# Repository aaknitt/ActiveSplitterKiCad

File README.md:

# ActiveSplitter Multicoupler
Hardware design for an active RF splitter for use with RTL-SDR receivers in the 100 MHz to 1 GHz band.  Not intended to be a piece of precision test equipment, but something inexpensive and "good enough" to use for general radio monitoring and scanning activities in a smaller and more convenient form factor than cable TV splitters or conventional higher end multicouplers.  

Uses amplifier circuit from [this LNA](https://github.com/fabiobaltieri/lna) design.

Design files are in KiCad format.

Estimated cost to build is $40 to $50 in low quantities with U.S. sourced parts.  Could be as low as $10 BOM cost with overseas sourcing and higher quantities.  

## NOTE: I've built one and it seems to function about as intended, but I haven't measured performance using real test equipment yet.  

- Designed to connect four RTL-SDR USB receivers to a single antenna without insertion loss.
- Amplifier circuit provides about 18 dB to 20 dB of gain.  Four way resistive divider results in 12 dB of loss per output, so total is about 6 dB of gain to each port.
- Amplifier is designed to be powered from an SDR providing 3 to 5 volts DC power to the J1 RF output port via a bias tee or from regulated external power.
- Spacing of the output SMA connectors is designed to accomodate plugging the SDR sticks directly into [this](https://www.amazon.com/gp/aw/d/B083XTKV8V) four-port powered USB hub.
- Main board and cover are PCBs.  "Sides" of the box are formed by .1" header pins soldered to each board.  The images show all pins populated, but only every fourth or so is probably need to provide sufficient RF shielding.
- Images below show using one SMA jack for the input and four SMA plugs for outputs connected directly to the RTL-SDR dongles.  However, these can all be substituted for varying SMA genders and orientations (90 degree vs. straight) to accomodate different configurations and cables.
- PCB footprints are included for 50 ohm terminating resistors for any unused outputs.  

## Questions for reviewers:
- Nearly all RF splitter/combiner circuits that I reviewed seemed to be carefuly about maintaining symmetry in the length of all PCB traces in each "branch" of the split.  How important is this, and why?  Is there an "acceptable" amount of assymetery relative to wavelength?  Giving up symmetry would likely allow the PCB to shrink in overall size a bit.  For example, could use a single 4-port splitter instead of two 2-port splits.  That should also increase port to port isolation across adjacent ports.  
- I had originally planned to include a Pi attenuator between the output of the amplifier and the first split to further knock down excessive gain from the amplifier so that insertion loss would cancel out gain.  As it stands, there will probably be about 6 to 8 dB of gain from input to each output.  Is there any reason that could cause problems?  Should I try to add the attenuator back in, even if it makes the overall size larger?
- Will the .1" pin headers create a reasonable Faraday cage instead of a solid housing?
- Is there any advantage or reason to combine R6 with R8  and R5 with R7?
- Should the splitter that starts with R6 be closer to R8 (same with R5/R7)?
- Is the circuit providing DC power to the amplifier (L1, L2, C2) reasonable?
- Should the values of C1 and C3 be changed to support the target range of 100 MHz to 1 GHz?

Assembled View:

Schematic [PDF](https://github.com/aaknitt/ActiveSplitterKiCad/blob/main/ActiveSplitterSchematic.pdf):

Main PCB View 1:

Main PCB View 2:

Cover PCB:

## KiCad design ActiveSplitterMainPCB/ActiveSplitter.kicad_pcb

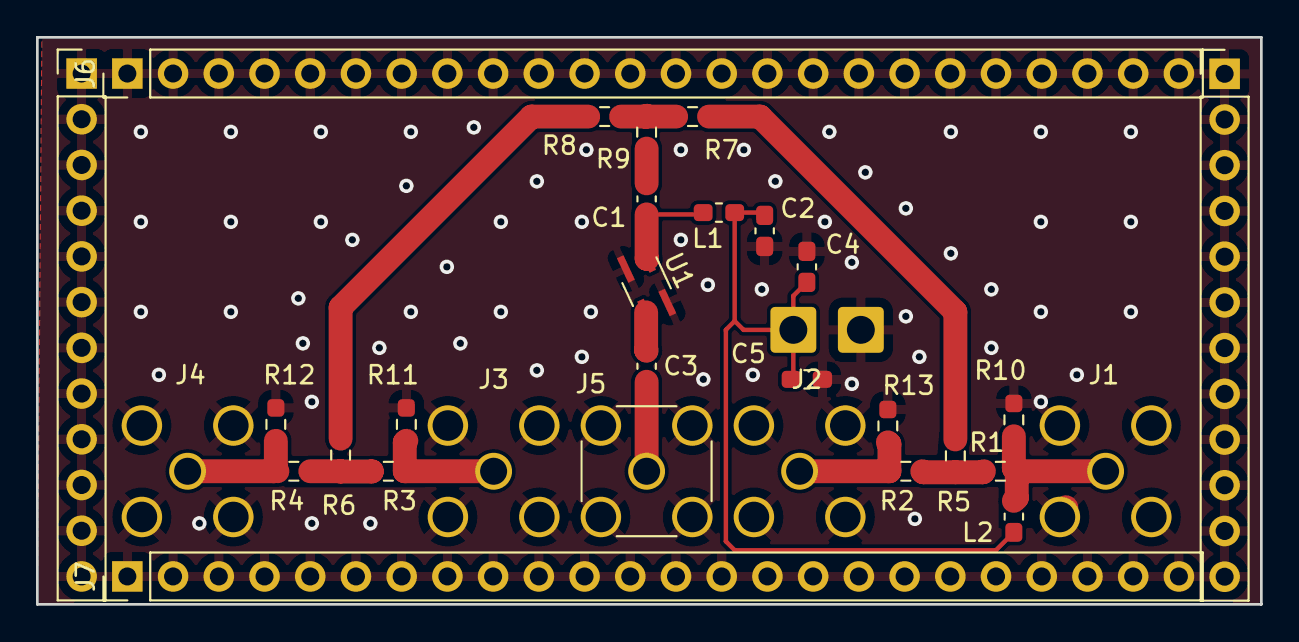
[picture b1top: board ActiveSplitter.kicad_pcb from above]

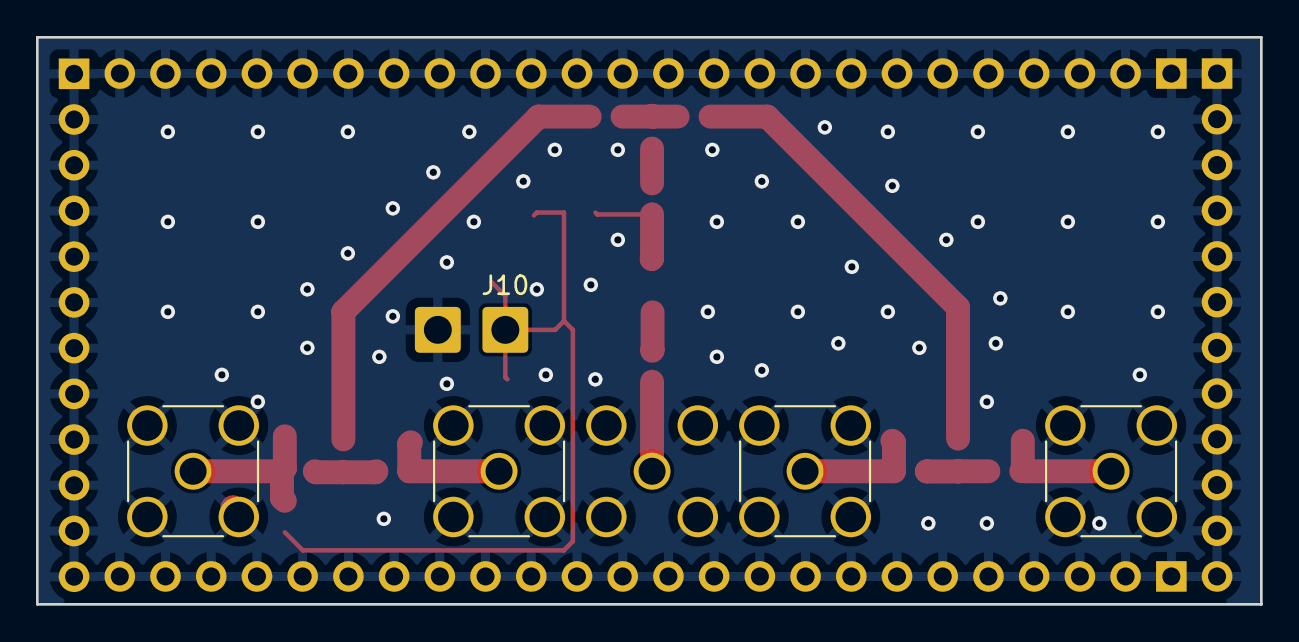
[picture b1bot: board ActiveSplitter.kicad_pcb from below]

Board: 2 copper layers, 68.0 x 31.5 mm, 32 parts (4 on the bottom side), 15 nets.

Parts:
C1, C3, C4, C5: 100p; C_0603_1608Metric_Pad1.08x0.95mm_HandSolder
C2: 10n; C_0603_1608Metric_Pad1.08x0.95mm_HandSolder
J1, J2, J3, J4: SMA_EDGE; SMA_Amphenol_132291_Vertical
J5: SMA_EDGE; SMA_Amphenol_132291-12_Vertical
J6, J7: Conn_01x24_Pin; PinHeader_1x24_P2.54mm_Vertical
J8, J9: Conn_01x12_Pin; PinHeader_1x12_P2.54mm_Vertical
J10, J11: Conn_01x01_Pin; SolderWire-0.75sqmm_1x01_D1.25mm_OD2.3mm
L1, L2: 200n; L_0603_1608Metric_Pad1.05x0.95mm_HandSolder
R1, R2, R3, R4, R5, R6, R7, R8, R9: 30; R_0603_1608Metric_Pad0.98x0.95mm_HandSolder
R10, R11, R12, R13: DNP; R_0603_1608Metric_Pad0.98x0.95mm_HandSolder
U1: PSA4-5043; SOT-343_SC-70-4_Handsoldering

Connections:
+3V3: C2.1, C4.1, C5.1, J10.1, L1.1, L2.2
GND: C2.2, C4.2, C5.2, J1.2, J2.2, J3.2, J4.2, J5.2, J6.1, J6.2, J6.3, J6.4, J6.5, J6.6, J6.7, J6.8, J6.9, J6.10, J6.11, J6.12, J6.13, J6.14, J6.15, J6.16, J6.17, J6.18, J6.19, J6.20, J6.21, J6.22, J6.23, J6.24, J7.1, J7.2, J7.3, J7.4, J7.5, J7.6, J7.7, J7.8, J7.9, J7.10, J7.11, J7.12, J7.13, J7.14, J7.15, J7.16, J7.17, J7.18, J7.19, J7.20, J7.21, J7.22, J7.23, J7.24, J8.1, J8.2, J8.3, J8.4, J8.5, J8.6, J8.7, J8.8, J8.9, J8.10, J8.11, J8.12, J9.1, J9.2, J9.3, J9.4, J9.5, J9.6, J9.7, J9.8, J9.9, J9.10, J9.11, J9.12, J11.1, R10.1, R11.1, R12.1, R13.1, U1.2 (GND), U1.4 (GND@1)
unnamed: C1.1, R9.1
unnamed: J1.1 (SIGNAL), L2.1, R1.1, R10.2
unnamed: J2.1 (SIGNAL), R2.1, R13.2
unnamed: J3.1 (SIGNAL), R3.1, R11.2
unnamed: J4.1 (SIGNAL), R4.1, R12.2
unnamed: C3.2, J5.1 (SIGNAL)
unnamed: R1.2, R2.2, R5.2
unnamed: R3.2, R4.2, R6.2
unnamed: R5.1, R7.2
unnamed: R6.1, R8.1
unnamed: R7.1, R8.2, R9.2
unnamed: C3.1, U1.3 (RF-IN)
unnamed: C1.2, L1.2, U1.1 (RF-OUT)

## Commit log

2023-12-10 Update LICENSE
2023-12-10 add termination resistors, PDF and SVG outputs for viewing
2023-12-10 add image of FreeCAD assembly with SDRS
2023-12-10 add schematic SVG
2023-12-10 Reduced output SMA spacing to 17mm to match USB hub. Added pad for external 3V supply.
2023-12-10 silkscreen cleanup
2023-12-12 fix keepout zones
2023-12-13 fix resistor values
2023-12-13 update size of cover PCB
